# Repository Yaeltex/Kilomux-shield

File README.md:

# Kilomux Shield
This is the Kilomux Arduino Shield repository, developed by Yaeltex in collaboration with Jorge Crowe from El Laboratorio del Juguete, both located in Buenos Aires, Argentina.

Kilomux is an Arduino UNO shield which expands the number of inputs and outputs using multiplexers and 74HC595 ICs and allows MIDI communication via USB or hardware.

Kilomux Arduino Library has a [new repo](https://github.com/Yaeltex/kilomux-arduino-library) now!

It has 16 digital outputs (without PWM for the moment) and 32 analog/digital inputs, which can be used independently with the provided functions. 
The shield has also 4 free digital pins (2, 3, 12 and 13 in v1, and 10, 11, 12 and 13 in v2), intended to connect an ultrasonic sensor, a button and an LED for its activation.

In the repository you can find whole HIDUINO repository - the firmware to send MIDI via USB and allow PC to recognize the Arduino as a MIDI device. In the "hiduino-master" folder you can find a tutorial on how to recompile (and rename) the firmware and load it into the Arduino device.

For more info, go to our [wiki](https://wiki.yaeltex.com/?nocache=1#.C2.B7_Kilomux_Shield) (in Spanish, for now)

If you have any questions, suggestions or comments about the shield, email us at franco (at) yaeltex.com.ar or post in [Yaeltex's forum](http://forum.yaeltex.com)

Cheers!

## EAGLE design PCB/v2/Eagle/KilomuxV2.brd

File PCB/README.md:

Para ver la lista de materiales entra al siguiente enlace:
https://cdn.rawgit.com/Yaeltex/KiloMux-Shield/master/PCB/KILO_MUX_SHIELD%20v1_bom.html

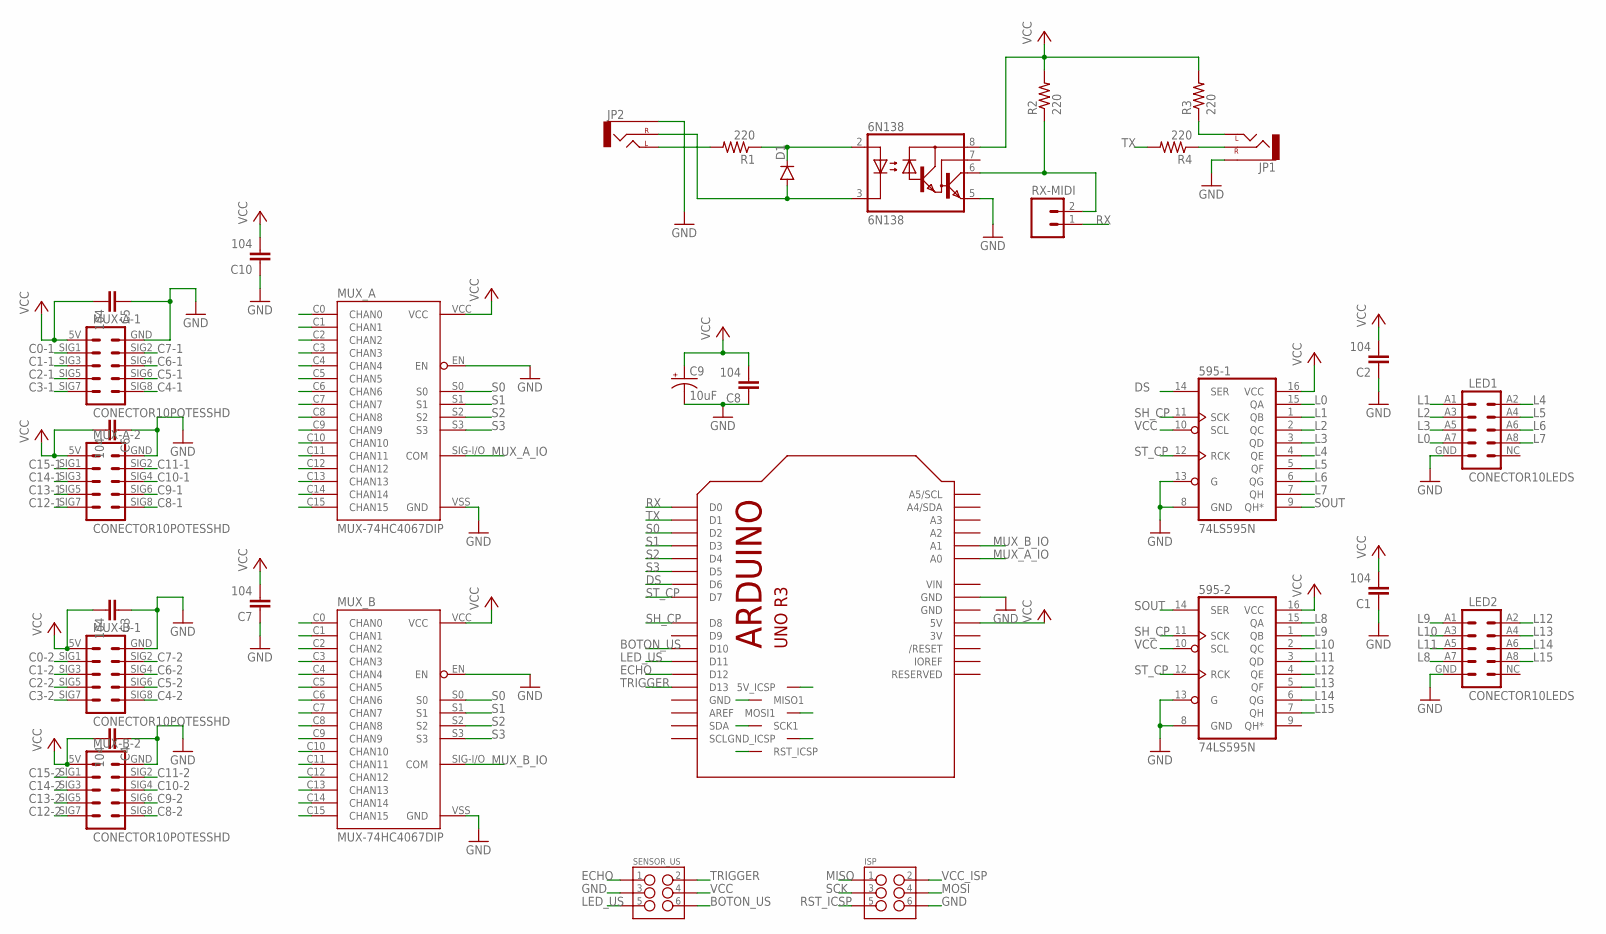
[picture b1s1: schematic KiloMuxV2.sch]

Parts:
6N138: 6N138; DIL08
595-1, 595-2: 74LS595N; DIL16
C1, C2, C3, C4, C5, C6, C7, C8, C10: 104; C025-025X050
C9: 10uF; CPOL-RADIAL-10UF-25V
D1: DIODE1N4148; DIODE-1N4148
ISP: M03X2NO_SILK; HEADER-2X3-MALE
JP1, JP2: AUDIO-JACKPTH; AUDIO-JACK
LED1, LED2: CONECTOR10LEDS; HEADER-2X5-MALE-LEDS
M1: ARDUINO_R3_ICSP; ARDUINOR3_ICSP
MUX-A-1, MUX-A-2: CONECTOR10POTESSHD; HEADER-2X3-MALE-POTES
MUX-B-1, MUX-B-2: CONECTOR10POTESSHD; HEADER-2X3-MALE-POTES
MUX_A: MUX-74HC4067DIP; DIL24
MUX_B: MUX-74HC4067DIP; DIL24
R1, R2, R3, R4: 220; 0207/10
RX-MIDI: M02PTH; 1X02
SENSOR_US: M03X2NO_SILK; HEADER-2X3-MALE

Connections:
3V: M1.3V
BOTON_US: M1.D10, SENSOR_US.6
C0-1: MUX-A-1.SIG1, MUX_A.C0 (CHAN0)
C0-2: MUX-B-1.SIG1, MUX_B.C0 (CHAN0)
C1-1: MUX-A-1.SIG3, MUX_A.C1 (CHAN1)
C1-2: MUX-B-1.SIG3, MUX_B.C1 (CHAN1)
C2-1: MUX-A-1.SIG5, MUX_A.C2 (CHAN2)
C2-2: MUX-B-1.SIG5, MUX_B.C2 (CHAN2)
C3-1: MUX-A-1.SIG7, MUX_A.C3 (CHAN3)
C3-2: MUX-B-1.SIG7, MUX_B.C3 (CHAN3)
C4-1: MUX-A-1.SIG8, MUX_A.C4 (CHAN4)
C4-2: MUX-B-1.SIG8, MUX_B.C4 (CHAN4)
C5-1: MUX-A-1.SIG6, MUX_A.C5 (CHAN5)
C5-2: MUX-B-1.SIG6, MUX_B.C5 (CHAN5)
C6-1: MUX-A-1.SIG4, MUX_A.C6 (CHAN6)
C6-2: MUX-B-1.SIG4, MUX_B.C6 (CHAN6)
C7-1: MUX-A-1.SIG2, MUX_A.C7 (CHAN7)
C7-2: MUX-B-1.SIG2, MUX_B.C7 (CHAN7)
C8-1: MUX-A-2.SIG8, MUX_A.C8 (CHAN8)
C8-2: MUX-B-2.SIG8, MUX_B.C8 (CHAN8)
C9-1: MUX-A-2.SIG6, MUX_A.C9 (CHAN9)
C9-2: MUX-B-2.SIG6, MUX_B.C9 (CHAN9)
C10-1: MUX-A-2.SIG4, MUX_A.C10 (CHAN10)
C10-2: MUX-B-2.SIG4, MUX_B.C10 (CHAN10)
C11-1: MUX-A-2.SIG2, MUX_A.C11 (CHAN11)
C11-2: MUX-B-2.SIG2, MUX_B.C11 (CHAN11)
C12-1: MUX-A-2.SIG7, MUX_A.C12 (CHAN12)
C12-2: MUX-B-2.SIG7, MUX_B.C12 (CHAN12)
C13-1: MUX-A-2.SIG5, MUX_A.C13 (CHAN13)
C13-2: MUX-B-2.SIG5, MUX_B.C13 (CHAN13)
C14-1: MUX-A-2.SIG3, MUX_A.C14 (CHAN14)
C14-2: MUX-B-2.SIG3, MUX_B.C14 (CHAN14)
C15-1: MUX-A-2.SIG1, MUX_A.C15 (CHAN15)
C15-2: MUX-B-2.SIG1, MUX_B.C15 (CHAN15)
DS: 595-1.14 (SER), M1.D6
ECHO: M1.D12, SENSOR_US.1
GND: 6N138.5 (GND), 595-1.8 (GND), 595-1.13 (G), 595-2.8 (GND), 595-2.13 (G), C1.1, C2.1, C3.1, C4.1, C5.1, C6.1, C7.1, C8.1, C9.2 (-), C10.1, ISP.6, JP1.SLEEVE, JP2.SLEEVE, LED1.GND, LED2.GND, M1.GND, M1.GND@1 (GND), M1.GND@2 (GND), M1.GND@4 (GND_ICSP), MUX-A-1.GND, MUX-A-2.GND, MUX-B-1.GND, MUX-B-2.GND, MUX_A.EN, MUX_A.VSS (GND), MUX_B.EN, MUX_B.VSS (GND), SENSOR_US.3
L0: 595-1.15 (QA), LED1.A7 (POS7)
L1: 595-1.1 (QB), LED1.A1 (POS1)
L2: 595-1.2 (QC), LED1.A3 (POS3)
L3: 595-1.3 (QD), LED1.A5 (POS5)
L4: 595-1.4 (QE), LED1.A2 (POS2)
L5: 595-1.5 (QF), LED1.A4 (POS4)
L6: 595-1.6 (QG), LED1.A6 (POS6)
L7: 595-1.7 (QH), LED1.A8 (POS8)
L8: 595-2.15 (QA), LED2.A7 (POS7)
L9: 595-2.1 (QB), LED2.A1 (POS1)
L10: 595-2.2 (QC), LED2.A3 (POS3)
L11: 595-2.3 (QD), LED2.A5 (POS5)
L12: 595-2.4 (QE), LED2.A2 (POS2)
L13: 595-2.5 (QF), LED2.A4 (POS4)
L14: 595-2.6 (QG), LED2.A6 (POS6)
L15: 595-2.7 (QH), LED2.A8 (POS8)
LED_US: M1.D11, SENSOR_US.5
MISO: ISP.1, M1.MISO1
MOSI: ISP.4, M1.MOSI1
MUX_A_IO: M1.A0, MUX_A.SIG-I/O (COM)
MUX_B_IO: M1.A1, MUX_B.SIG-I/O (COM)
unnamed: JP2.TIP (LEFT), R1.2
unnamed: 6N138.3 (C), D1.A, JP2.RING (RIGHT)
unnamed: 6N138.2 (A), D1.C, R1.1
unnamed: 6N138.6 (VO), R2.1, RX-MIDI.2
unnamed: JP1.TIP (LEFT), R3.1
unnamed: JP1.RING (RIGHT), R4.1
RST_ICSP: ISP.5, M1.RESET_ICSP1 (RST_ICSP)
RX: M1.D0, RX-MIDI.1
S0: M1.D2, MUX_A.S0, MUX_B.S0
S1: M1.D3, MUX_A.S1, MUX_B.S1
S2: M1.D4, MUX_A.S2, MUX_B.S2
S3: M1.D5, MUX_A.S3, MUX_B.S3
SCK: ISP.3, M1.SCK1
SH_CP: 595-1.11 (SCK), 595-2.11 (SCK), M1.D8
SOUT: 595-1.9 (QH*), 595-2.14 (SER)
ST_CP: 595-1.12 (RCK), 595-2.12 (RCK), M1.D7
TRIGGER: M1.D13, SENSOR_US.2
TX: M1.D1, R4.2
VCC: 6N138.8 (VCC), 595-1.10 (SCL), 595-1.16 (VCC), 595-2.10 (SCL), 595-2.16 (VCC), C1.2, C2.2, C3.2, C4.2, C5.2, C6.2, C7.2, C8.2, C9.1 (+), C10.2, M1.5V, MUX-A-1.5V, MUX-A-2.5V, MUX-B-1.5V, MUX-B-2.5V, MUX_A.VCC, MUX_B.VCC, R2.2, R3.2, SENSOR_US.4
VCC_ISP: ISP.2, M1.5V_ICSP1 (5V_ICSP)
VIN: M1.VIN

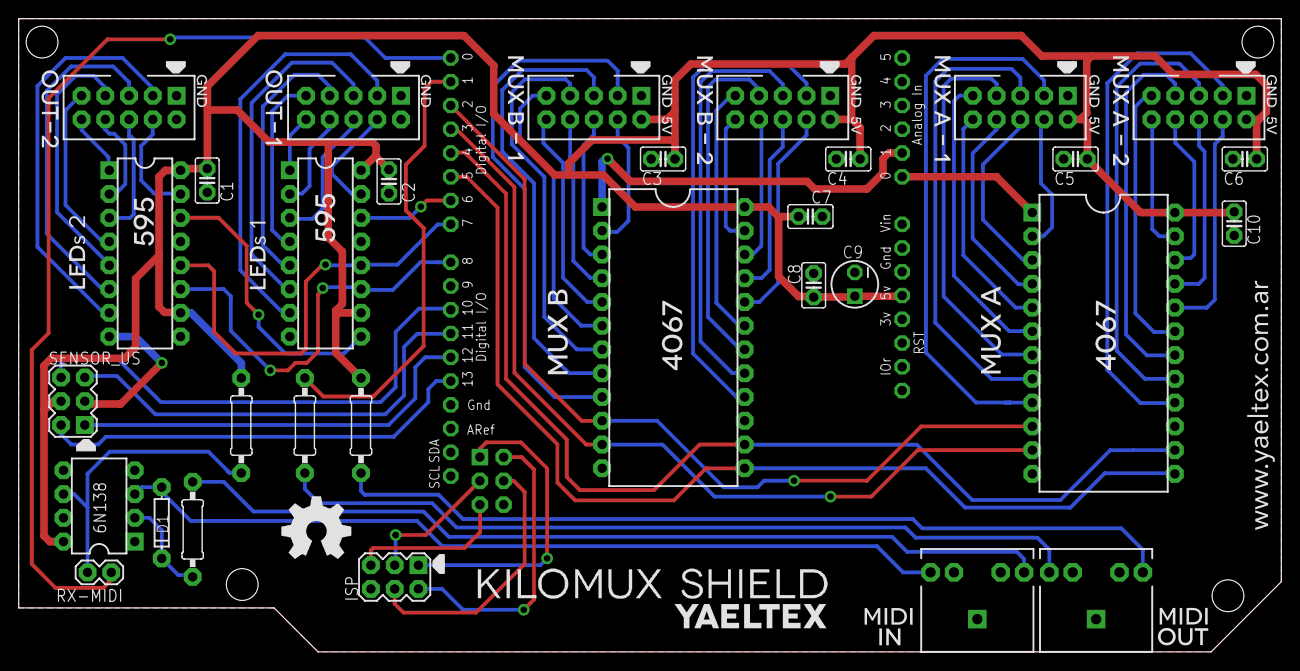
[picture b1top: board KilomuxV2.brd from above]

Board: 2 copper layers, 135.0 x 67.7 mm, 32 parts (0 on the bottom side), 77 nets.

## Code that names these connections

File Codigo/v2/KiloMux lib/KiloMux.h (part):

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  #define UMBRAL_DIFERENCIA_US 80        // 
  #define FILTRO_US            3         // Cantidad de valores almacenados para el filtro. Cuanto más grande, mejor el suavizado y  más lenta la lectura.
  // FIJOS - NO CAMBIAR!!!
  #define TRIGGER_PIN          13        // Pin de arduino conectado al pin de trigger del sensor
  #define ECHO_PIN             12        // Pin de arduino conectado al pin de echo del sensor
  #define PIN_BOTON_ACT_US     10        // Pin de arduino conectado al botón que activa el sensor
  #define PIN_LED_ACT_US       11        // Pin de arduino conectado al led que indica la activación del sensor
  #define MAX_US               MAX_DISTANCIA*US_ROUNDTRIP_CM   // Maximo tiempo en microsegundos que dura el pulso en retornar
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// VARIABLES y OBJETOS ///////////////////////////////////////////////////////////////////
//////////////////////////////////////////////////////////////////////////////////////////
#if defined(CON_ULTRASONIDO)
NewPing sensorUS(TRIGGER_PIN, ECHO_PIN, MAX_DISTANCIA); // Instancia de NewPing para el sensor US.
int ccSensorValuePrev[FILTRO_US];                       
#endif

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
// Variables para los registros de desplazamiento
const int dataPin = 6;                             // Pin de datos (DS) conectado al pin 14 del 74HC595
const int latchPin = 7;                            // Pin de latch (ST_CP) conectado al pin 12 del 74HC595
const int clockPin = 8;                            // Pin de clock (SH_CP) conectado al pin 11 del 74HC595
boolean registros[NUM_LEDS_X_BANCO];                       // Estado de los LEDs (HIGH - 1 o LOW - 0) para uso de las funciones que escriben el 74HC595.
unsigned int estadoLeds[BANCOS][NUM_LEDS_X_BANCO];    // Estado de todos los bancos de LEDs

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
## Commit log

2015-05-26 :octocat: Added .gitattributes & .gitignore files
2015-05-27 KiloMux Shield
    El KiloMux es un shield para Arduino UNO que expande la cantidad de
    entradas y salidas usando multiplexores e integrados 79HC595 y permite
    la comunicación via MIDI, ya sea por USB o por hardware.
    Se tienen 16 salidas digitales (por ahora sin PWM) y 32 entradas con la
    posibilidad de combinar 16 digitales y 16 analógicas o 32 analógicas o
    32 digitales. El shield tiene también libres los pines 2, 3, 12 y 13,
2015-05-27 Corrección en el PCB
    Se corrigió la posición del rectángulo en el PCB del KiloMux
2015-05-27 Revert "KiloMux Shield"
    This reverts commit d45241305f9d1b27c13db9e6093eab8ca5d7117d.
    Conflicts:
    PCB/KILO_MUX_SHIELD v1.fzz
2015-05-27 Upload de todos los archivos
2015-05-27 Cambio de nombres
2015-05-27 Agregado README
2015-05-27 Añadido README
2015-05-27 Cambio de nombre
2015-05-27 Codigo unificado con y sin ultrasonido. Se especifica comentando o descomentando un define
2015-05-27 mejora menor a la lectura del sensor ultrasonico
2015-05-28 Comunicacion por midi y sensor de ultrasonido por defecto
2015-05-28 define para Hairless midi
2015-05-28 Correción de comentarios
2015-05-28 Arreglado el problema con los defines
2015-05-28 Correcciones de codigo para compilacion y sensor de ultrasonido
2015-05-28 Añadida la BOM y correcciones en el PCB
2015-05-28 Correccion en el codigo, los includes no dependen del tipo de comunicacion
2015-05-29 Link para lista de materiales
2015-05-29 Cambio de titulo
2015-05-29 Actualizacion de la visualizacion HTML
2015-06-09 Mejorada la funcion esRuido, y añadida la opcion de modo TOGGLE a los botones
2015-06-16 Mejorada la funcion de filtrado de ruido
2015-06-17 Añadida la funcionalidad de hasta 3 shifters. Se apagan los leds si se recibe cualquier NoteOff, ademas de si se recibe NoteOn con velocity 0
2015-06-17 Agregada arduino_midi.hex
2015-08-04 corrección 74hc595
2015-08-04 correccion de errores de tipeo
2015-08-04 Agregada la version 2 del KiloMux Shield
2015-08-05 Corregidos los pines libres de la v1 y v2
2015-08-05 Agregado el codigo y las librerias necesarias para la v2 del KiloMux Shield
2015-08-05 Innecesario
2015-08-05 Eliminado el codigo viejo
2015-08-06 Añadido README.md
2015-08-06 Cambio de nombre de carpeta
2015-08-06 Codigo de arduino para la v2 del KiloMux
2015-08-06 Modif README
2015-08-06 Reestructuracion de la carpeta Codigo
2015-08-06 Reestructuracion de la carpeta
2015-08-06 Añadida la version de codigo para la v1 del KiloMux
2015-08-06 Reubicacion del proyecto hiduino
2015-08-06 Traducción del README.md.
    Resolves Yaeltex/KiloMux-Shield#1
2015-08-06 Added the forum link in the README files
2015-08-06 Deleted doc folder
2015-08-06 Added forum link to README files
2015-08-07 Añadida datasheet del sensor HC-SR04
2015-09-19 New KiloMux Shield Library v1.0
2015-09-19 Some names changed to english
2015-09-19 Removed folder
2015-09-19 Added zip file
2015-10-16 Added wiki to README
2015-10-27 Replaced and corrected label orientation for digital outputs
2015-10-27 Minor change to README
2015-11-13 Restructure
2015-11-14 Corrected minor typos
2015-11-14 Corrected filename
2015-11-14 No changes
2015-11-14 Deleted extra folder
2015-11-17 Added Eagle files zip
2015-12-09 Updated hiduino and README
2016-02-04 Rename Arduino Library -> Arduino Code
2016-02-16 Revised library examples, and added spanish version for ultrasonic
2016-02-16 Minor name change
2016-02-16 Corrected schematic
2016-02-18 Test
2016-02-18 Included header in examples
2016-02-19 Library name change
2016-02-19 Kilomux is the new name
2016-02-19 removed old lib
2016-02-19 Added new lib
2016-02-19 Changed zip name
2016-02-19 Removed old PCB
2016-02-19 Added new PCB folder
2016-02-29 License CC in english
2016-03-02 Moved examples
2016-03-09 Added example LedMatrix
2016-03-10 Añadida versión en español de ejemplo con matriz de LEDs
2016-04-06 Changes to readme and lib
2016-04-06 Changes to readme
2016-04-10 Updated licenses and comments in library
2016-04-10 Link in README
2016-04-10 Link in README changed
2016-04-29 Añadido v3 del controlador midi con el Kilomux
2016-04-29 Cambios al README
2016-04-29 Actualizado el README
2016-05-02 Se agrega al codigo la opcion de activar y desactivar entradas, y elegir si son analogicas o digitales
2016-05-19 Minor bug fix
2016-06-02 Renamed folder of KM Library
2016-07-04 Changed input numbers from 1-16 to 0-15 in lirary and examples
2016-07-12 New version of Kilomux Lib, and updated examples
2016-08-26 Added init() function to library and examples
2016-08-26 Updated zip file for Kilomux lib
2016-08-26 Updated constructor
2016-10-07 Minor changes
2016-10-07 Mistake
2016-10-07 v4 midi controller multi file in progress
2016-10-10 Cambios menores a README
2016-12-16 Faster read, with port manipulation
2017-01-20 Reversed unwanted change
2017-01-20 Adapted to work with Kilowhat. Still work to do
2017-01-20 Updated next steps
2017-01-30 Save instance
2017-01-30 Original working code
2017-01-30 Original code (now for real)
2017-01-30 Fixed min-max kilowhat config
2017-03-14 Updated to work with Kilowhat
2017-03-30 Removed kilomux lib because there is a new git repo for it
2017-03-30 Moved hiduino folder
2017-03-31 Removed hiduino rep copy and added a mocolufa hex renamed Kilomux
2017-05-18 Added LICENSE file

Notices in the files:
Codigo/v2/KiloMux lib/KiloMux.h:
Creative Commons Atribución-CompartirIgual 4.0 Internacional - http://creativecommons.org/licenses/by-sa/4.0
